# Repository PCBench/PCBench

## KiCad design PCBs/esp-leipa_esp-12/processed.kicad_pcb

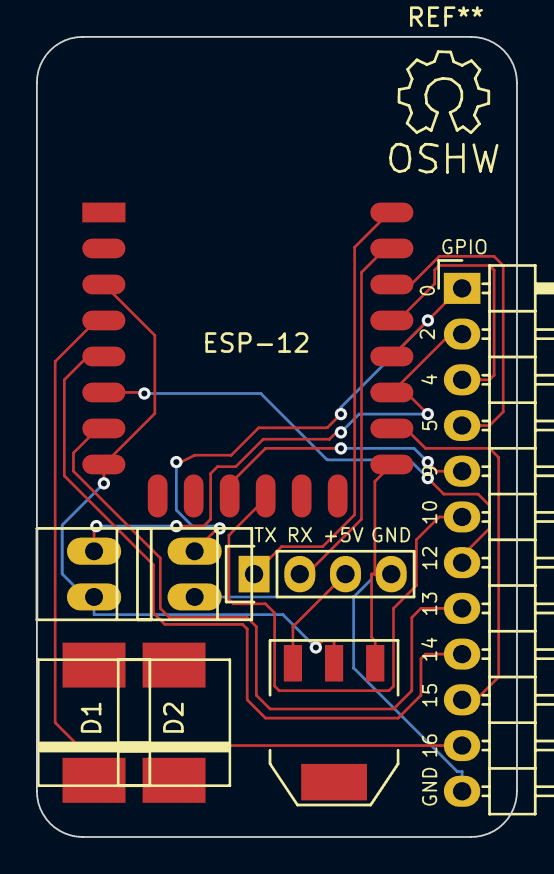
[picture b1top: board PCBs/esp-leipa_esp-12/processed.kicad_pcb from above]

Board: 2 copper layers, 26.7 x 44.4 mm, 8 parts (0 on the bottom side), 16 nets.

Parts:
D1, D2: D; DIODE_DO214AB-SMC
ESP-12: ESP-12E
F1, F2: JUMPER; PINHEAD1-2
P1: CONN_01X12; Pin_Header_Angled_1x12
P2: UART; Pin_Header_Straight_1x04
U1: LD1117S33TR; SOT-223

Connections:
+5V: P2.3, U1.3
EN: ESP-12.3, ESP-12.8, F2.2, U1.2
GND: ESP-12.15, F1.2, P1.12, P2.4, U1.1
GPIO0: ESP-12.18, F1.1, P1.1
GPIO2: ESP-12.17, F2.1, P1.2
GPIO4: ESP-12.19, P1.3
GPIO5: ESP-12.20, P1.4
GPIO9: ESP-12.11, P1.5
GPIO10: ESP-12.12, P1.6
GPIO12: ESP-12.6, P1.7
GPIO13: ESP-12.7, P1.8
GPIO14: ESP-12.5, P1.9
GPIO15: ESP-12.16, P1.10
GPIO16: ESP-12.4, P1.11
RXD0: ESP-12.21, P2.2
TXD0: ESP-12.22, P2.1

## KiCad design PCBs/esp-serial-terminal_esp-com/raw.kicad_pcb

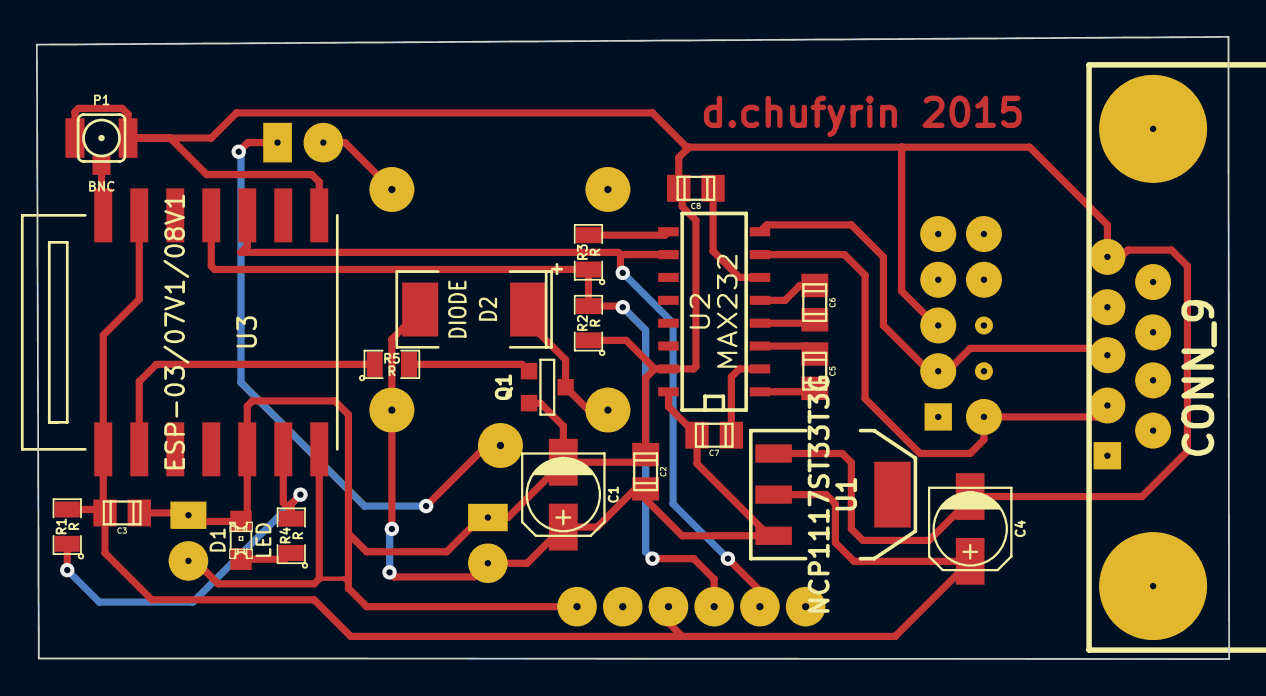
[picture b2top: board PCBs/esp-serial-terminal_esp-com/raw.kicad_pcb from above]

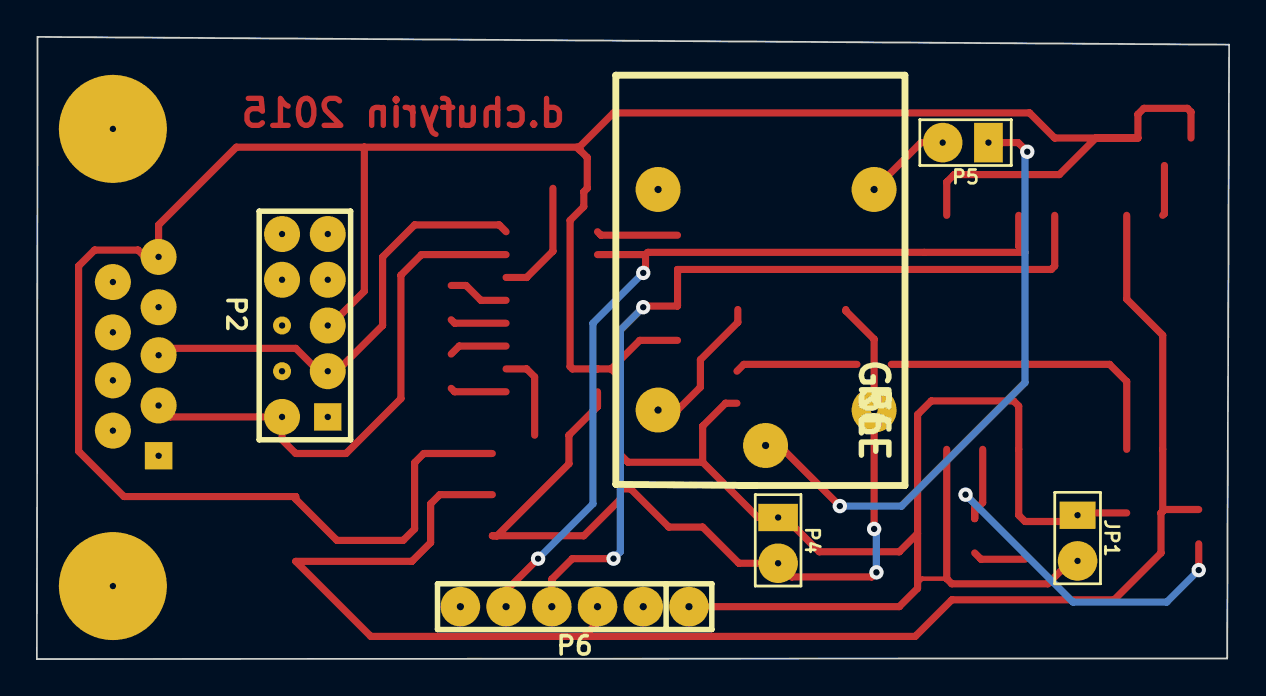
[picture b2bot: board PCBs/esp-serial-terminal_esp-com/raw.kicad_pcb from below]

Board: 2 copper layers, 66.2 x 34.6 mm, 27 parts (6 on the bottom side), 22 nets.

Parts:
C1: CP1; c_elec_4x5.8
C2, C3, C5, C6, C7, C8: C; c_0805
C4: CP1; c_elec_4x5.7
D1: LED; LED-0805
D2: DIODE; SM2512
JP1: JUMPER; PIN_ARRAY_2X1
P1: BNC; coaxial_u.fl-r-smt-1
P2: CONN_5X2; PIN_ARRAY_5x2
P3: CONN_9; DB9MC
P4, P5: CONN_2; PIN_ARRAY_2X1
P6: CONN_6; PIN_ARRAY-6X1
Q1: NPN; SOT23EBC
R1, R2, R3, R4, R5: R; SM0805
R6: G5LE
U1: NCP1117ST33T3G; SOT223
U2: MAX232; SO16E
U3: ESP-03/07V1/08V1; ESP-03

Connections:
+5V: C1.1, C2.1, C7.1, D2.2, P4.2, R6.2, U1.3, U2.16
GND: C1.2, C2.2, C3.2, C4.2, C8.1, D1.2, JP1.1, JP1.2, P1.2, P2.5, P3.5, P4.1, P6.1, Q1.1, R2.1, U1.1, U2.15, U3.5, U3.7, U3.8
unnamed: P2.2, P3.2, U2.7
unnamed: P2.3, P3.3, U2.8
unnamed: D2.1, Q1.3, R6.1
unnamed: C7.2, U2.2
unnamed: C8.2, U2.6
unnamed: C5.2, U2.3
unnamed: C5.1, U2.1
unnamed: C6.1, U2.4
unnamed: C6.2, U2.5
unnamed: R3.2, U2.9
unnamed: P6.4, R2.2, R3.1, U3.11
unnamed: P1.1, U3.14
unnamed: R5.1, U3.2
unnamed: D1.1, R4.1
unnamed: Q1.2, R5.2
unnamed: P5.2, R6.5
unnamed: P5.1, R6.4
unnamed: P6.5, U2.10, U3.10
unnamed: R1.1, R4.2, U3.6
unnamed: C3.1, C4.1, P6.3, R1.2, U1.2, U3.1, U3.13

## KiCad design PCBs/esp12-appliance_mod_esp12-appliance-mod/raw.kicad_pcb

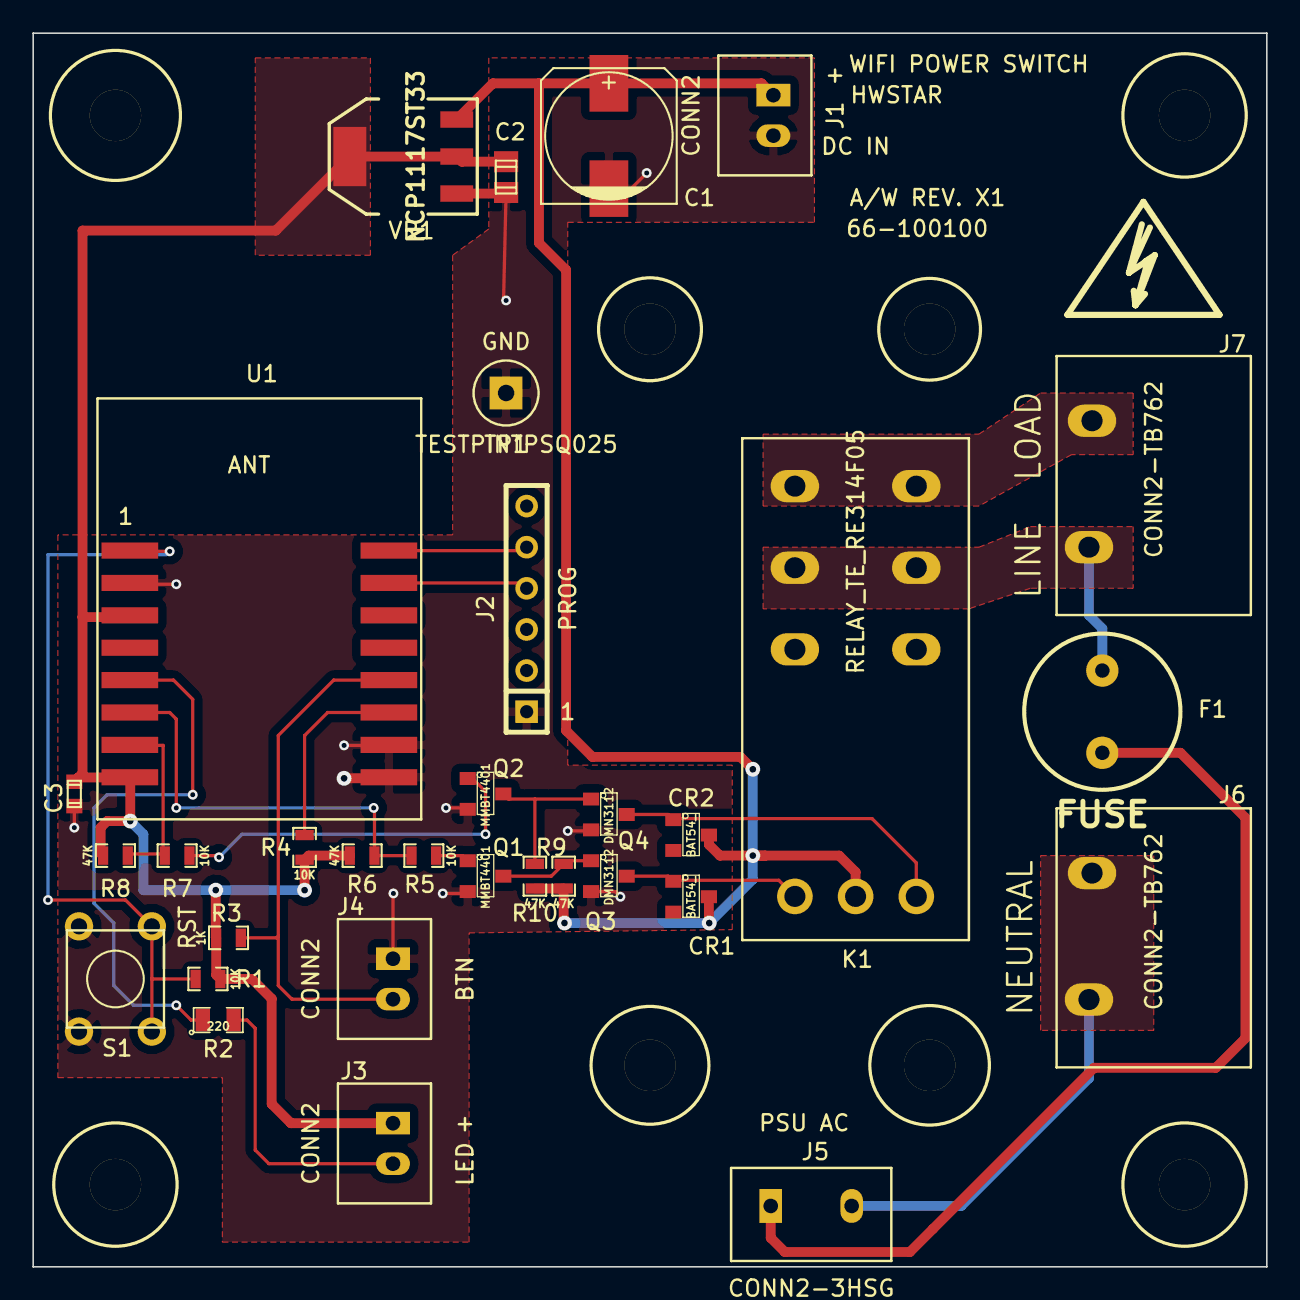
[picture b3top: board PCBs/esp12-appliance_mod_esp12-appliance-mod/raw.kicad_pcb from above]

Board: 2 copper layers, 76.2 x 76.2 mm, 41 parts (0 on the bottom side), 22 nets.

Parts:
C1: 470; c_elec_8x10
C2: 10U; c_0805
C3: 0.1U; c_0603
CR1, CR2: BAT54_; SOT23
F1: FUSE; BELFUSE_MRT
J1, J3, J4: CONN2; JST_B2B_XH_A
J2: CONN6; SIL-6
J5: CONN2-3HSG; JST_B3B_SPECIAL
J6, J7: CONN2-TB762; 7R62vertscrewterm2pos
K1: RELAY_TE_RE314F05; RELAY_TE_RE314F
MTGHOLE125, MTGHOLE125#2, MTGHOLE125#3, MTGHOLE125#4, MTGHOLE125#5, MTGHOLE125#6, MTGHOLE125#7, MTGHOLE125#8: VAL**; MTGHOLE125
Q1, Q2: MMBT4401; SOT23
Q3, Q4: DMN3112; SOT23
R1, R4, R5, R7: 10K; SM0603_Resistor
R2: 220; SM0805
R3: 1K; SM0603_Resistor
R6, R8, R9, R10: 47K; SM0603_Resistor
S1: SW_TACT; SW_TACT_6MM
Sym: Symbol_HighVoltage_Type2_SilkTop_VerySmall
TP1: TESTPINTPSQ025; TESTPIN
U1: ESP8266-ESP-12; ESP8266-ESP12
VR1: NCP1117ST33; SOT223

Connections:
+3.3V: C2.1, C3.1, J3.1, R1.1, R3.1, R4.1, R6.1, R8.1, U1.3, U1.8, VR1.2, VR1.4
+5V: C1.1, CR1.3, CR2.3, J1.1, K1.A3, R9.1, R10.1, VR1.3
/CLEAR: CR2.1, K1.A1, Q4.3
/RXD: J2.4, U1.15
/SET: CR1.1, K1.A2, Q3.3
/TXD: J2.5, U1.16
/~RST: R1.2, S1.1, S1.2, U1.1
GND: C1.2, C2.2, C3.2, J1.2, J2.1, J4.1, Q1.2, Q2.2, Q3.2, Q4.2, S1.3, S1.4, TP1.1, U1.2, U1.9, U1.10, VR1.1
unnamed: F1.1, J5.1
unnamed: F1.2, J7.1, K1.11A, K1.11B
unnamed: J3.2, R2.2
unnamed: J4.2, R3.2, U1.12
unnamed: J5.2, J6.1, J6.2
unnamed: J7.2, K1.14A, K1.14B
unnamed: Q1.1, R5.1
unnamed: Q1.3, Q3.1, R9.2
unnamed: Q2.1, R7.1
unnamed: Q2.3, Q4.1, R10.2
unnamed: R2.1, U1.5
unnamed: R4.2, U1.11
unnamed: R5.2, R6.2, U1.6
unnamed: R7.2, R8.2, U1.7

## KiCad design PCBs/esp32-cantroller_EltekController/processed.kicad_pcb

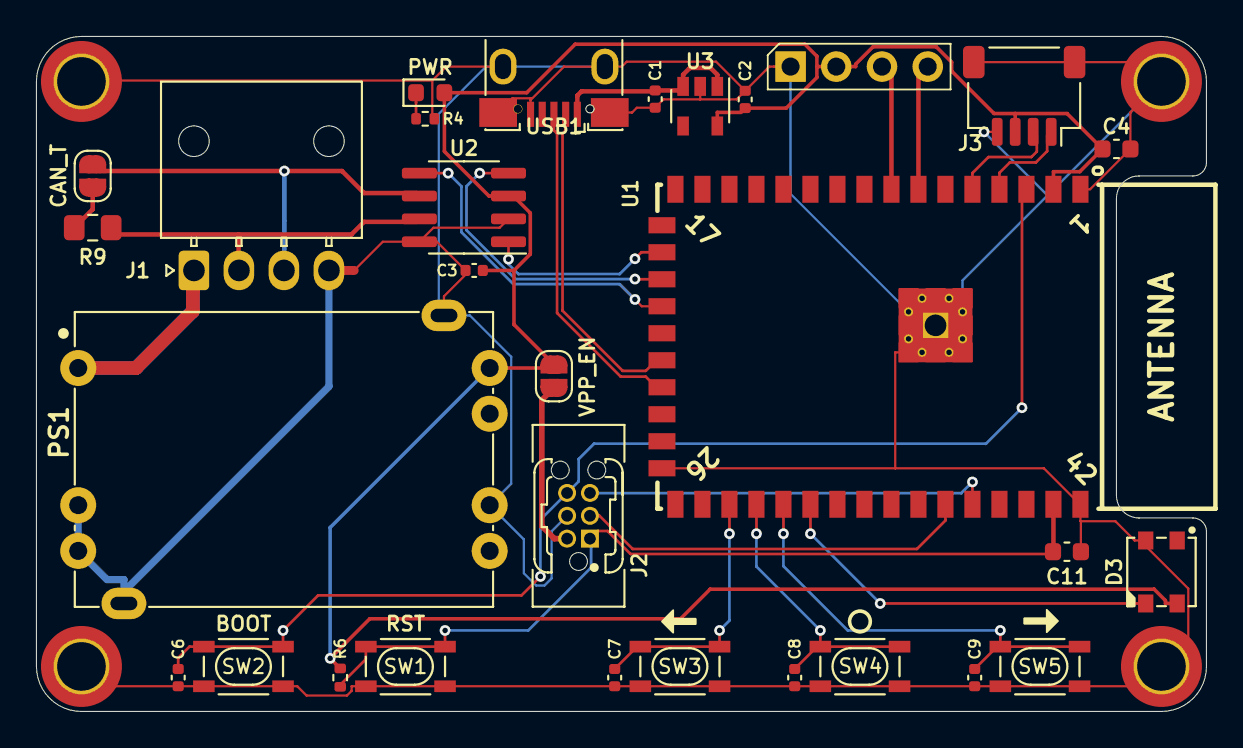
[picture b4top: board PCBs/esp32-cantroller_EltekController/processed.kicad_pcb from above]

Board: 2 copper layers, 65.0 x 37.5 mm, 36 parts (1 on the bottom side), 27 nets.

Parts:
C1, C2, C3: 10uF; C_0402_1005Metric
C4: 22uF; C_0603_1608Metric
C6, C7, C8, C9: 100nF; C_0402_1005Metric
C11: 10uF; C_0603_1608Metric
D2: PWR; LED_0603_1608Metric_SnapModel
D3: SK6812MINI; LED_SK6812MINI_PLCC4_3.5x3.5mm_P1.75mm_3D
H1, H2, H3, H4: MP; MountingHole_2.7mm_M2.5_ISO7380_Pad_TopBottom
I2C1: OLED; OLED_SSD1315_128x64_1.3_I2C_New_Silhouette_Big3D
J1: CANBUS; Molex_Nano-Fit_105313-xx04_1x04_P2.50mm_Horizontal_3D
J2: ESP-PROG; Gecko-G125_PlusTC2030_IDCBox_2x03_P1.25mm_Vertical_3D
J3: Qwiic; JST_SH_SM04B-SRSS-TB_1x04-1MP_P1.00mm_Horizontal_3D
JP1: VPP_EN; SolderJumper-2_P1.3mm_Open_RoundedPad1.0x1.5mm
JP2: CAN_T; SolderJumper-2_P1.3mm_Open_RoundedPad1.0x1.5mm
LOGO1: Logo_Open_Hardware_Small; neggle-logo-0.12
NT1: GND_TIE; NetTie-2_SMD_Pad0.5mm
PS1: CC3-4803SF-E; Converter_DCDC_TDK-Lambda_CC3-xxxxxF-E
R4: 1K; R_0402_1005Metric
R6: 10K; R_0402_1005Metric
R9: 120R; R_0805_2012Metric_Pad1.15x1.40mm_HandSolder
SW1: RST; KEY-SMD_4P-L4.2-W3.2-P2.20-LS5.1-TL
SW2: BOOT; KEY-SMD_4P-L4.2-W3.2-P2.20-LS5.1-TL
SW3: LEFT; KEY-SMD_4P-L4.2-W3.2-P2.20-LS5.1-TL
SW4: SEL; KEY-SMD_4P-L4.2-W3.2-P2.20-LS5.1-TL
SW5: RIGHT; KEY-SMD_4P-L4.2-W3.2-P2.20-LS5.1-TL
U1: ESP32-S2-WROVER; ESP32-S2-WROVER_and_WROOM(PCB,-I(IPEX))-Universal
U2: MAX3051ESA; SOIC-8_3.9x4.9mm_P1.27mm
U3: XC6220B331MR; SOT-23-5
USB1: USB; MICRO-USB-SMD_U254-051T-4BH83-F1S_C397452

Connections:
+3V3: C2.2, C3.2, C4.2, D2.2, D3.4, I2C1.2, J3.3, JP1.1, PS1.7, R6.2, U1.2, U2.3, U3.5
+48V: J1.1, PS1.1
/CAN+: J1.2, R9.1, U2.7
/CAN-: J1.3, JP2.2, U2.6
/CAN_RX: U1.19, U2.4
/CAN_TX: U1.18, U2.1
/LED_D: D3.3, U1.32
/OLED_SCL: I2C1.3, U1.8
/OLED_SDA: I2C1.4, U1.7
/QW_SCL: J3.1, U1.4
/QW_SDA: J3.2, U1.5
/U0RXD: J2.5, U1.38
/U0TXD: J2.3, U1.37
/USB_D+: U1.23, USB1.3
/USB_D-: U1.22, USB1.2
/VBUS: C1.2, U3.1, U3.3, USB1.1
/VPP: J2.2, JP1.2
/~BOOT: C6.2, J2.6, SW2.1, U1.3
/~CAN_EN: U1.20, U2.5
/~RST: C11.1, J2.1, R6.1, SW1.1, U1.41
/~SW_L: C7.2, SW3.1, U1.29
/~SW_R: C9.2, SW5.1, U1.31
/~SW_S: C8.2, SW4.1, U1.30
GND: C1.1, C2.1, C3.1, C4.1, C6.1, C7.1, C8.1, C9.1, C11.2, D3.2, H1.1, H2.1, H3.1, H4.1, I2C1.1, J2.4, J3.4, J3.MP, NT1.2, PS1.5, PS1.MP2, R4.1, SW1.2, SW2.2, SW3.2, SW4.2, SW5.2, U1.1, U1.26, U1.42, U1.43, U2.2, U2.8, U3.2, USB1.5, USB1.6
GNDPWR: J1.4, NT1.1, PS1.2, PS1.3, PS1.MP
unnamed: D2.1, R4.2
unnamed: JP2.1, R9.2

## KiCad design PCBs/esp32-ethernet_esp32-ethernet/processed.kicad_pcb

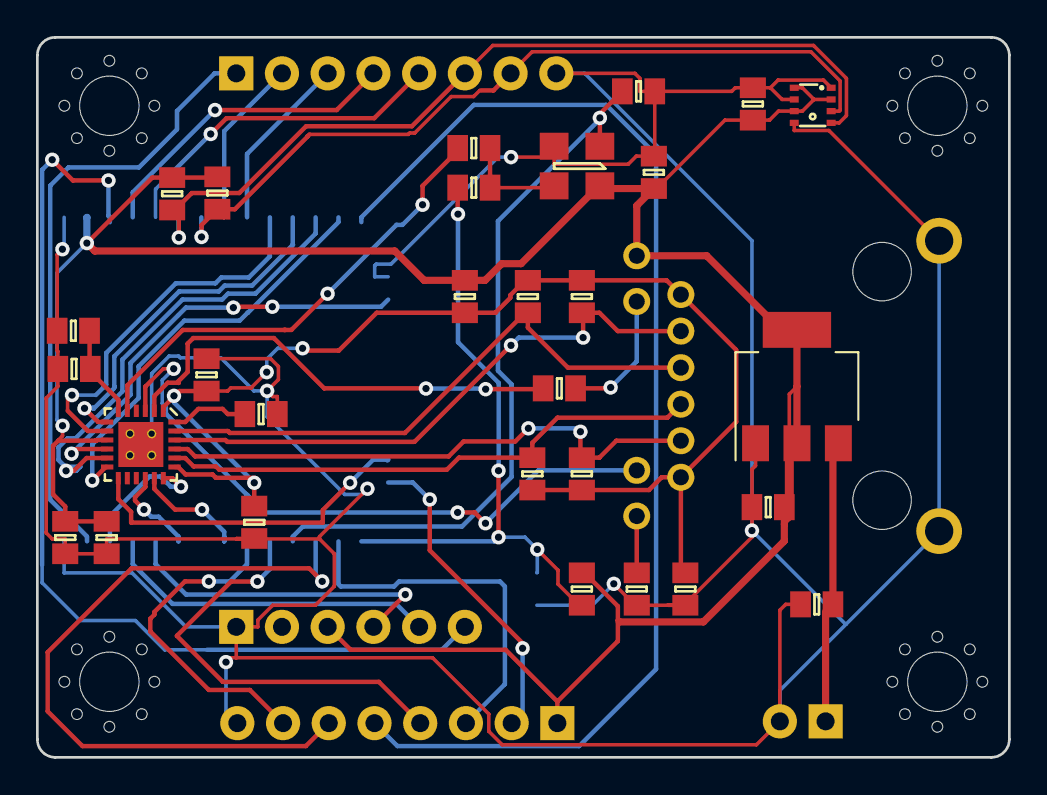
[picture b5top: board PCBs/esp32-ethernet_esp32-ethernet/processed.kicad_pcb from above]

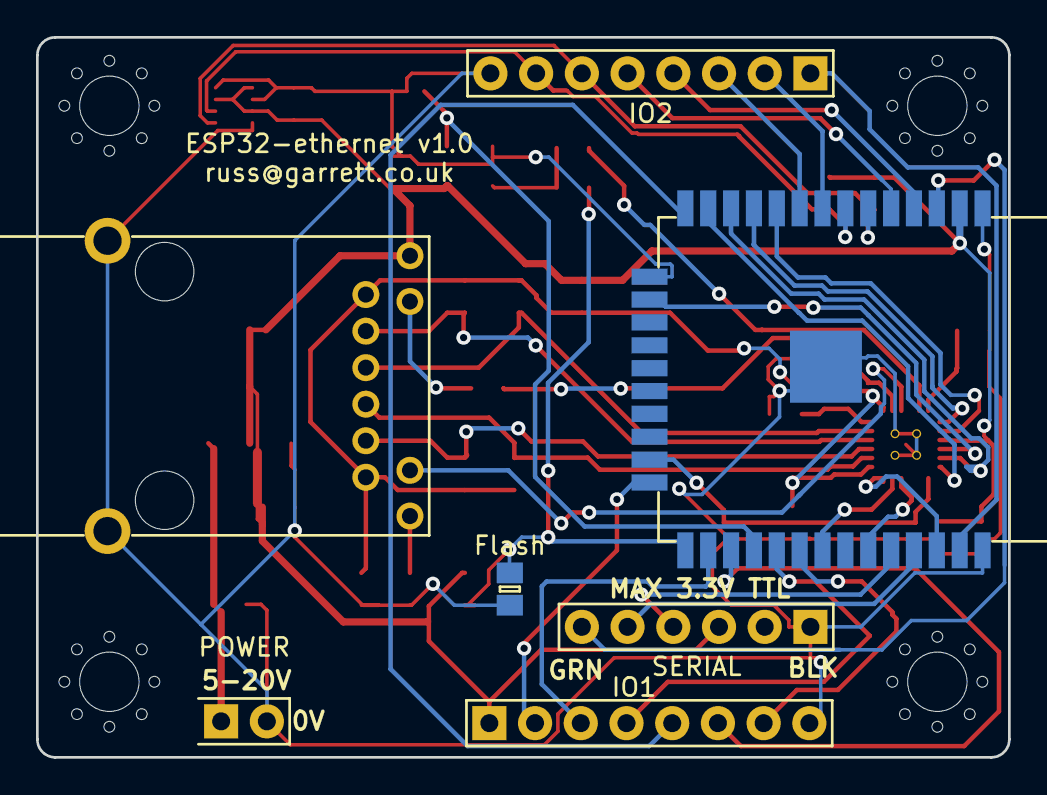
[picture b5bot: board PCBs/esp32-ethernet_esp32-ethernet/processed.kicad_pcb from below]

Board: 2 copper layers, 54.0 x 40.0 mm, 36 parts (7 on the bottom side), 43 nets.

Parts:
C1, C4, C5, C8, C9, C11: 0.1u; 0805
C2: 10u 50V; 0805
C3: 22u; 0805
C6: 10u; 0805
C7: 1u; 0805
C10: 470p; 0805
IC1: BME280
IC2: ESP-WROOM-32
IC3: NCP1117-3.3; SOT-223
IC4: LAN8720A; QFN-24-EP-MICROCHIP
IC5: RJMG16x; RJMG16X
J1: SERIAL; SIL-254P-06
J2: POWER; DIL-254P-02
J3: IO1; SIL-254P-08
J4: IO2; SIL-254P-08
JP1: Flash; 0805
L1: Bead; 0805
R1, R2: 4.7K; 0805
R3, R6: 4.7k; 0805
R4, R5: R; 0805
R7, R8, R10, R11: 49.9; 0805
R9: 12.1k 1%; 0805
R12, R13: 270; 0805
Y1: SG5032CAN 50MHz; SG5032CxN

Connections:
3v3: C1.1, C3.1, C6.1, C9.1, C11.2, IC1.2, IC1.6, IC1.8, IC2.2, IC3.2, IC3.4, IC4.9, IC5.10, J1.3, J3.1, L1.1, R1.1, R2.1, R3.1, Y1.4
/LAN_PHY/CLK: IC4.5, R5.2
/LAN_PHY/MDC: IC2.23, IC4.13
/LAN_PHY/MDIO: IC2.13, IC4.12
/LAN_PHY/RXD0: IC2.10, IC4.8
/LAN_PHY/RXD1: IC2.11, IC4.7
/LAN_PHY/RXER: IC2.16, IC4.10
/LAN_PHY/RX_DV: IC2.12, IC4.11
/LAN_PHY/TXD0: IC2.31, IC4.17
/LAN_PHY/TXD1: IC2.36, IC4.18
/LAN_PHY/TXEN: IC2.33, IC4.16
GND: C1.2, C2.2, C3.2, C4.2, C5.2, C6.2, C7.2, C8.2, C9.2, C10.2, C11.1, IC1.1, IC1.5, IC1.7, IC2.1, IC2.15, IC2.38, IC2.39, IC3.1, IC4.EP, IC5.S, J1.1, J2.2, J3.8, J4.8, JP1.1, R6.2, R9.1, R12.2, Y1.2
GPIO2: IC2.24, J3.2
GPIO4: IC2.26, J3.3
GPIO5: IC2.29, J3.4
GPIO12: IC2.14, J3.5
GPIO16: IC2.27, J3.6
GPIO18: IC2.30, J3.7
GPIO23: IC2.37, J4.1
GPIO32: IC2.8, J4.2
GPIO33: IC2.9, J4.3
GPIO36: IC2.4, J4.4
GPIO39: IC2.5, J4.5
I2C_SCL: IC1.4, IC2.6, J4.6, R1.2
I2C_SDA: IC1.3, IC2.7, J4.7, R2.2
LAN_VDD: C4.1, C5.1, C8.1, IC4.1, IC4.19, IC5.1, IC5.6, L1.2, R7.2, R8.2, R10.2, R11.2
LED1: IC4.3, IC5.8
LED2: IC4.2, R13.1
unnamed: C2.1, IC3.3, J2.1
unnamed: C7.1, C10.1, IC4.6
unnamed: IC2.3, J1.6
unnamed: IC2.25, JP1.2, R3.2, R4.2
unnamed: IC2.34, J1.4
unnamed: IC2.35, J1.5
unnamed: IC4.20, IC5.3, R8.1
unnamed: IC4.21, IC5.2, R7.1
unnamed: IC4.22, IC5.5, R11.1
unnamed: IC4.23, IC5.4, R10.1
unnamed: IC4.24, R9.2
unnamed: IC5.7, R12.1
unnamed: IC5.9, R13.2
PHY_CLK: R4.1, R5.1, Y1.3
PHY_CLK_EN: IC2.28, R6.1, Y1.1

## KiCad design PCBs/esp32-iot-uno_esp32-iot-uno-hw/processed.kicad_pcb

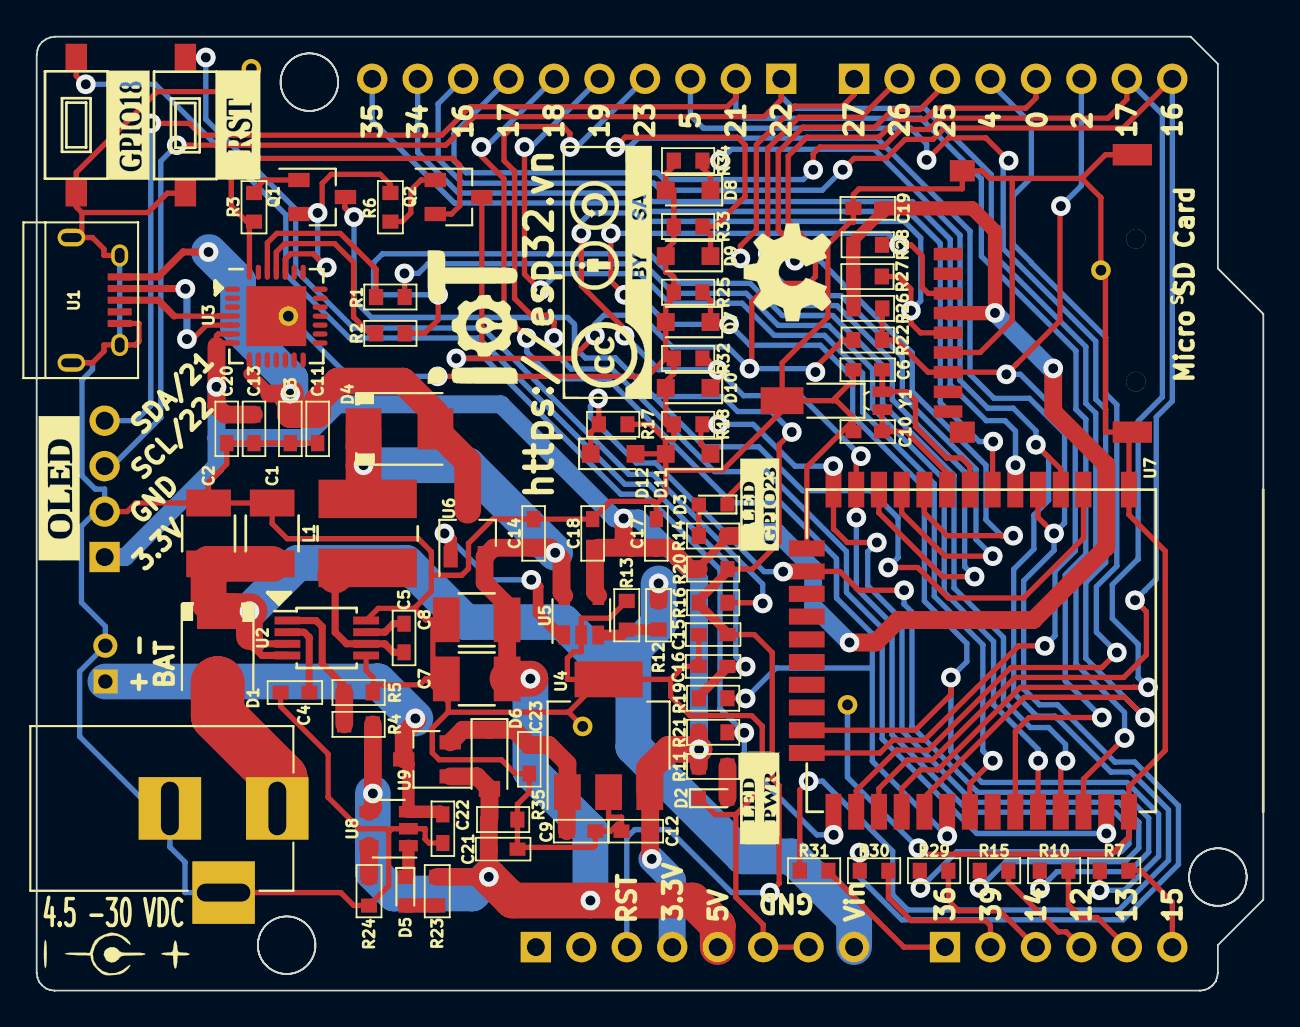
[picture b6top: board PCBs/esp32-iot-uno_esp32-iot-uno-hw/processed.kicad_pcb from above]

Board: 2 copper layers, 68.5 x 53.3 mm, 91 parts (0 on the bottom side), 62 nets.

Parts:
BAT1: BAT; Pin_Header_Straight_2x01_Pitch2.00mm
C1, C2: 10uF/50V; C_1210
C3, C18, C20: 10uF; C_0603
C4, C9, C11, C12, C13, C23: 1uF; C_0603
C5, C14: 100nF; C_0603
C6, C10: 27pF/50V; C_0603
C7, C8: 10uF/25V; C_1210
C15, C16: 0.1uF/50V; C_0603
C17: 0.1uF; C_0603
C19: 10uF/25V; C_0603
C21, C22: 4,7uF; C_0603
CON1: BARREL_JACK
D1, D4: SS34; do214aa-g
D2: Led_PWR_G; LED_0603
D3: LED_IO23_W; LED_0603
D5: Led; LED_0603
D6: BAT60JFILM; D_SOD-123
D7, D8, D9, D10, D11, D12: D_Zener_3.3V; D_SOD-323_HandSoldering
L1: 22uH; Choke_SMD_Wuerth-WE-PD2-Typ-MS
P1, P2: GPIO; Pin_Header_Straight_1x08_Pitch2.54mm
P3: ADC; Pin_Header_Straight_1x06_Pitch2.54mm
P4: GPIO; Pin_Header_Straight_1x10_Pitch2.54mm
P5: OLED; Pin_Header_Straight_1x04_Pitch2.54mm
Q1, Q2: S8050_NPN_BEC; SOT-23_standar
R1, R2, R11, R14, R16, R19, R23: 470R; R_0603
R3, R6, R24: 10K; R_0603
R4: 52.5K; R_0603
R5, R12, R13, R20: 10k; R_0603
R7, R10, R15, R29, R30, R31: 33R/1%; R_0603
R17, R18, R25, R32, R33, R34: NC/1%; R_0603
R21, R22, R26, R27, R28: 10k/1%; R_0603
R35: 100K; R_0603
S1: SD_CARD; MicroSD_Push-Push-A
SW1: SW_EN; Tact_Switch_TS6X3.6
SW2: SW_IO18; Tact_Switch_TS6X3.6
U1: usb_mini_b; USB_Micro-B
U2: MCP16311-MNY; MSOP-8_3x3mm_Pitch0.65mm
U3: CP2102; QFN-28-1EP_5x5mm_Pitch0.5mm
U4: TC1264-3.3VDBTR; SOT-223-3Lead_TabPin2
U5: MCP601OT; SOT-23-5
U6: IRLM6402; SOT-23_standar
U7: ESP32; ESP-WROOM-32
U8: MCP73831/2; SOT-23-5
U9: DMP1045U; SOT-23_standar
Y1: 32.768KHz; Crystal_SMD_MicroCrystal_MS3V-T1R

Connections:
+3V3: C12.1, C13.1, C17.1, C18.1, C19.1, C20.1, P1.4, P5.1, R11.1, R14.1, R20.2, R21.2, R26.2, R27.2, R28.2, S1.4, U3.6, U3.7, U4.3, U5.4, U7.2
+5V: C7.1, C8.1, C14.1, C21.1, D4.1, D6.2, L1.2, P1.5, R4.1, R23.2, R35.2, U5.5, U6.2, U8.4, U9.1
+5VD: C9.1, C23.1, D6.1, U4.1, U9.2
A0/IO36: P3.1, R31.2
A1/IO39: P3.2, R30.2
A2/IO14: P3.3, R29.2
A3/IO12: P3.4, R15.2
A4/IO13: P3.5, R10.2
A5/IO15: P3.6, R7.2
ADC1_0/IO36: D8.1, R31.1, R34.2, U7.4
ADC1_3/IO39: D9.1, R30.1, R33.2, U7.5
ADC2_0/IO4: P2.4, U7.26
D+: U1.3, U3.4
D-: U1.2, U3.5
DTR: Q2.2, R3.1, U3.28
EN: C15.1, P1.3, Q1.3, R16.1, R20.1, U7.3
GND: BAT1.2, C1.2, C2.2, C3.2, C4.2, C6.2, C7.2, C8.2, C9.2, C10.2, C11.2, C12.2, C13.2, C14.2, C15.2, C16.2, C17.2, C18.2, C19.2, C20.2, C21.2, C22.2, C23.2, CON1.2, CON1.3, D2.1, D7.2, D8.2, D9.2, D10.2, D11.2, D12.2, P1.6, P1.7, P5.2, R5.2, R13.1, R17.1, R18.1, R24.1, R25.1, R32.1, R33.1, R34.1, R35.1, S1.6, S1.11, S1.12, SW1.2, SW2.1, U1.5, U1.6, U2.5, U2.8, U4.2, U5.2, U7.1, U7.15, U7.38, U8.2, Y1.3
IO0: P2.5, Q2.3, R21.1, R22.1, U7.25
IO2/DATA0: P2.6, R22.2, R26.1, S1.7, U7.24
IO5: P4.3, U7.29
IO12: D11.1, R15.1, R18.2, U7.14
IO13: D12.1, R10.1, R17.2, U7.16
IO14/CLK: D10.1, R27.1, R29.1, R32.2, S1.5, U7.13
IO15/CMD: D7.1, R7.1, R25.2, R28.1, S1.3, U7.23
IO16/U2RXD: P2.8, P4.8, U7.27
IO17/U2TXD: P2.7, P4.7, U7.28
IO18: P4.6, R19.1, U7.30
IO19: P4.5, U7.31
IO21/SDA: P4.2, P5.4, U7.33
IO22/SCL: P4.1, P5.3, U7.36
IO23: D3.1, P4.4, U7.37
IO25: P2.3, U7.10
IO26: P2.2, U7.11
IO27: P2.1, U7.12
IO32: C6.1, U7.8, Y1.1
IO33: C10.1, U7.9, Y1.2
IO34: P4.9, U7.6
IO35: P4.10, U7.7
unnamed: BAT1.1, C22.1, U8.3, U9.3
unnamed: C4.1, U2.2
unnamed: C5.1, U2.7
unnamed: C5.2, L1.1, U2.6
unnamed: C16.1, R19.2, SW2.2
unnamed: CON1.1, D1.2
unnamed: D2.2, R11.2
unnamed: D3.2, R14.2
unnamed: D5.1, U8.1
unnamed: D5.2, R23.1
unnamed: Q1.1, R3.2
unnamed: Q2.1, R6.2
unnamed: R4.2, R5.1, U2.1
unnamed: R12.1, R13.2, U5.3
unnamed: R16.2, SW1.1
unnamed: R24.2, U8.5
unnamed: U5.1, U6.1
RTS: Q1.2, R6.1, U3.24
RXD: R1.1, U7.34
RXD_CP2102: R2.2, U3.25
TXD: R2.1, U7.35
TXD_CP2102: R1.2, U3.26
VCC: C3.1, C11.1, D4.2, U1.1, U3.8, U6.3
Vin: C1.1, C2.1, D1.1, P1.8, R12.2, U2.3, U2.4

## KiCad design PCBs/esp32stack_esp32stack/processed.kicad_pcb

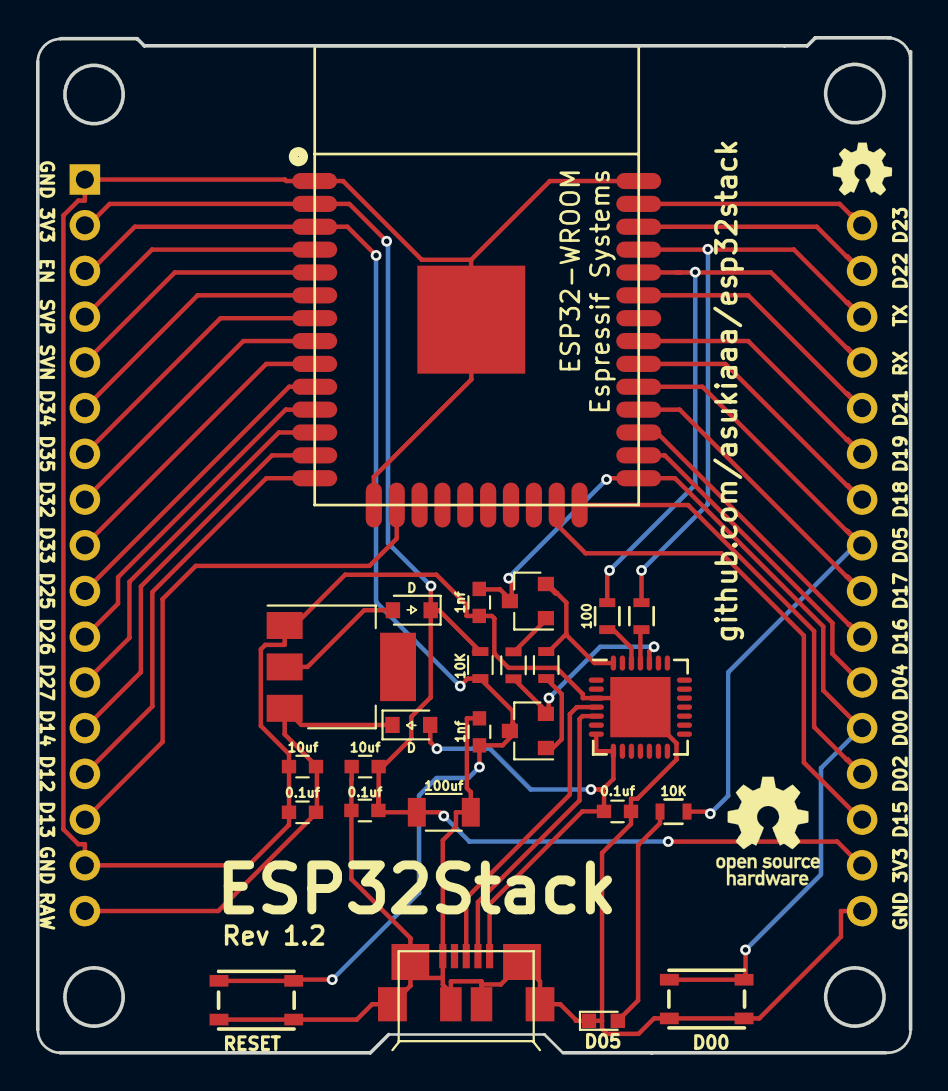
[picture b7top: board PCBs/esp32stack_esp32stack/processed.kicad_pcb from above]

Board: 2 copper layers, 48.5 x 56.4 mm, 27 parts (0 on the bottom side), 41 nets.

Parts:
C1, C2: 1nf; C_0603
C3, C4: 10uf; C_0603
C5, C6, C7: 0.1uf; C_0603
C8: 100uf; C_1206
D1, D2: D; D_0805
D3: D05; LED_0603
J1: CONN_01X17; Pin_Header_Straight_1x17_Pitch2.54mm
J2: CONN_01X16; Pin_Header_Straight_1x16_Pitch2.54mm
P1: USB_OTG; USB_MICRO_B-HIROSE-ZX62R-B-5P
Q1, Q2: MMBT3904; SOT-23
R1, R2, R3, R4: 10K; R_0603
R5, R6: 100; R_0603
SW1, SW2: SWITCH_SPST; SKRPACE010
U1: ESP32-WROOM
U2: NCP1117ST33T3G; SOT-223
U3: CP2102; QFN-28-1EP_5x5mm_Pitch0.5mm

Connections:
+3V3: C3.1, C7.1, C8.1, D2.1, J1.2, J2.15, R3.2, U1.2
+5V: C6.1, D1.2, P1.1, U3.7, U3.8
D+: P1.3, U3.4
D-: P1.2, U3.5
DTR: Q2.2, R1.1, U3.28
EN: C1.1, J1.3, Q1.3, R3.1, SW2.1, U1.3
GND: C1.2, C2.2, C3.2, C4.2, C5.2, C6.2, C7.2, C8.2, D3.1, J1.1, J1.16, J2.16, P1.5, P1.6, SW1.2, SW2.2, U1.1, U1.15, U1.38, U1.39, U2.1, U3.3, U3.29
IO0(boot): C2.1, J2.12, Q2.3, SW1.1, U1.25
IO2: J2.13, U1.24
IO4: J2.11, U1.26
IO5: J2.8, R4.1, U1.29
IO12: J1.14, U1.14
IO13: J1.15, U1.16
IO14: J1.13, U1.13
IO15: J2.14, U1.23
IO16: J2.10, U1.27
IO17: J2.9, U1.28
IO18: J2.7, U1.30
IO19: J2.6, U1.31
IO21: J2.5, U1.33
IO22: J2.2, U1.36
IO23: J2.1, U1.37
IO25: J1.10, U1.10
IO26: J1.11, U1.11
IO27: J1.12, U1.12
IO32: J1.8, U1.8
IO33: J1.9, U1.9
IO34: J1.6, U1.6
IO35: J1.7, U1.7
unnamed: D2.2, U2.2
unnamed: D3.2, R4.2
unnamed: Q1.1, R1.2
unnamed: Q2.1, R2.2
unnamed: R5.2, U3.25
unnamed: R6.2, U3.26
RTS: Q1.2, R2.1, U3.24
RXDtoTXD0: J2.3, R5.1, U1.35
SVN: J1.5, U1.5
SVP: J1.4, U1.4
TXDtoRXD0: J2.4, R6.1, U1.34
VCC: C4.1, C5.1, D1.1, J1.17, U2.3
